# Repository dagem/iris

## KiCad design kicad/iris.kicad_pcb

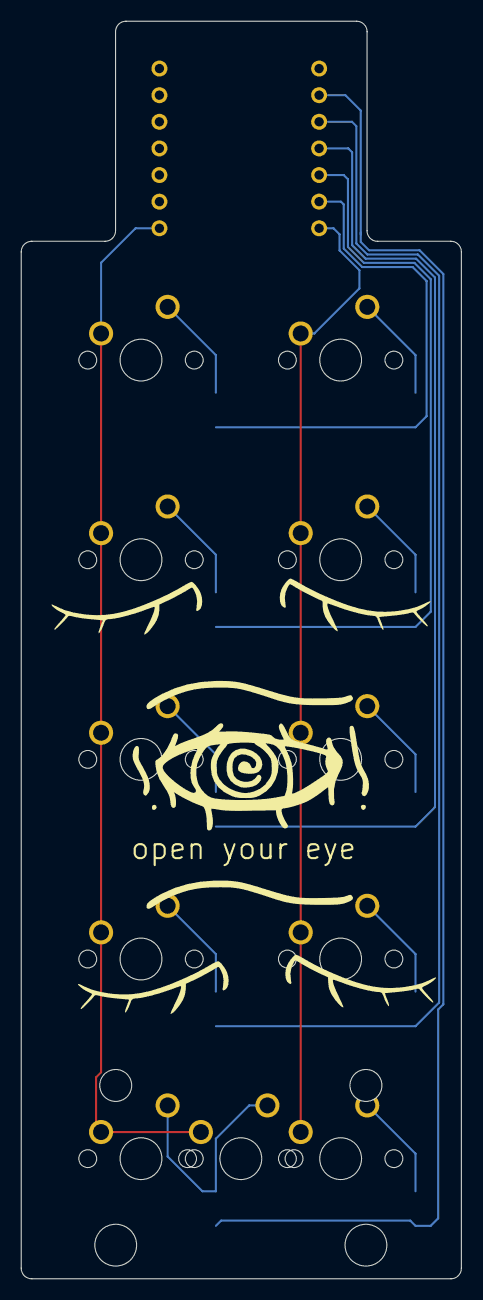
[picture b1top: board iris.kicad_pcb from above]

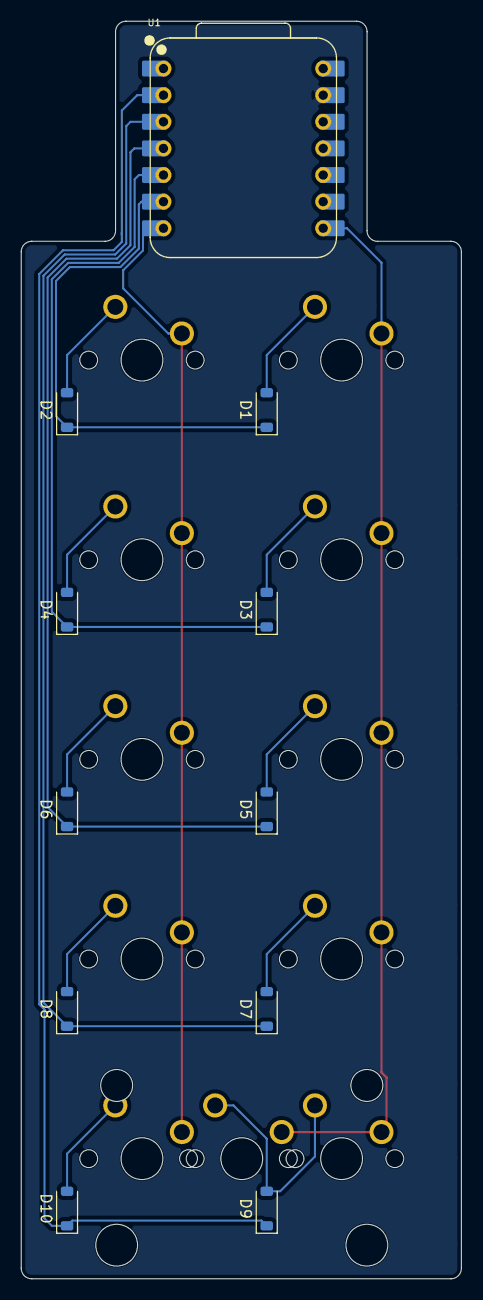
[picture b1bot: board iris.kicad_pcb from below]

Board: 2 copper layers, 42.0 x 120.0 mm, 22 parts (11 on the bottom side), 17 nets.

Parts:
D1, D2, D3, D4, D5, D6, D7, D8, D9, D10: SOD-123; D_SOD-123
MX1, MX2, MX3, MX4, MX5, MX6, MX7, MX8, MX9, MX10: MX-NoLED; MX-Solderable-1U
MX11: MX-NoLED; MX-Solderable-2U
U1: XIAO-RP2040-SMD; XIAO-RP2040-DIP

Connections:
COL0: MX1.1, MX3.1, MX5.1, MX7.1, MX9.1, MX11.1, U1.8 (GPIO1_D7_CSn_RX)
COL1: MX2.1, MX4.1, MX6.1, MX8.1, MX10.1, U1.7 (GPIO0_D6_TX)
unnamed: D1.2 (A), MX1.2
unnamed: D2.2 (A), MX2.2
unnamed: D3.2 (A), MX3.2
unnamed: D4.2 (A), MX4.2
unnamed: D5.2 (A), MX5.2
unnamed: D6.2 (A), MX6.2
unnamed: D7.2 (A), MX7.2
unnamed: D8.2 (A), MX8.2
unnamed: D9.2 (A), MX9.2, MX11.2
unnamed: D10.2 (A), MX10.2
ROW0: D1.1 (K), D2.1 (K), U1.6 (GPIO7_D5_SCL)
ROW1: D3.1 (K), D4.1 (K), U1.5 (GPIO6_D4_SDA)
ROW2: D5.1 (K), D6.1 (K), U1.4 (GPIO29_A3_D3)
ROW3: D7.1 (K), D8.1 (K), U1.3 (GPIO28_A2_D2)
ROW4: D9.1 (K), D10.1 (K), U1.2 (GPIO27_A1_D1)

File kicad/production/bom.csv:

Designator,Footprint,Quantity,Value,LCSC Part #
"D1, D10, D2, D3, D4, D5, D6, D7, D8, D9",D_SOD-123,10,SOD-123,
"MX1, MX10, MX2, MX3, MX4, MX5, MX6, MX7, MX8, MX9",MX-Solderable-1U,10,MX-NoLED,
MX11,MX-Solderable-2U,1,MX-NoLED,
U1,XIAO-RP2040-DIP,1,XIAO-RP2040-SMD,

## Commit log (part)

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2026-05-24 feat: set up kicad project and directory
2026-05-25 feat: finish pcb layout
2026-05-25 feat: create initial part design for iris case
2026-05-25 feat: add silkscreen art to pcb
2026-05-25 feat: update case and pcb to near production ready
2026-05-25 fix: remove .DS_Store files
2026-05-25 fix: updated .gitignore
2026-05-27 feat: update case to prototype production unit
2026-05-29 feat: update case to v2 prototype
2026-06-02 fix: proper clearance for pcb top
